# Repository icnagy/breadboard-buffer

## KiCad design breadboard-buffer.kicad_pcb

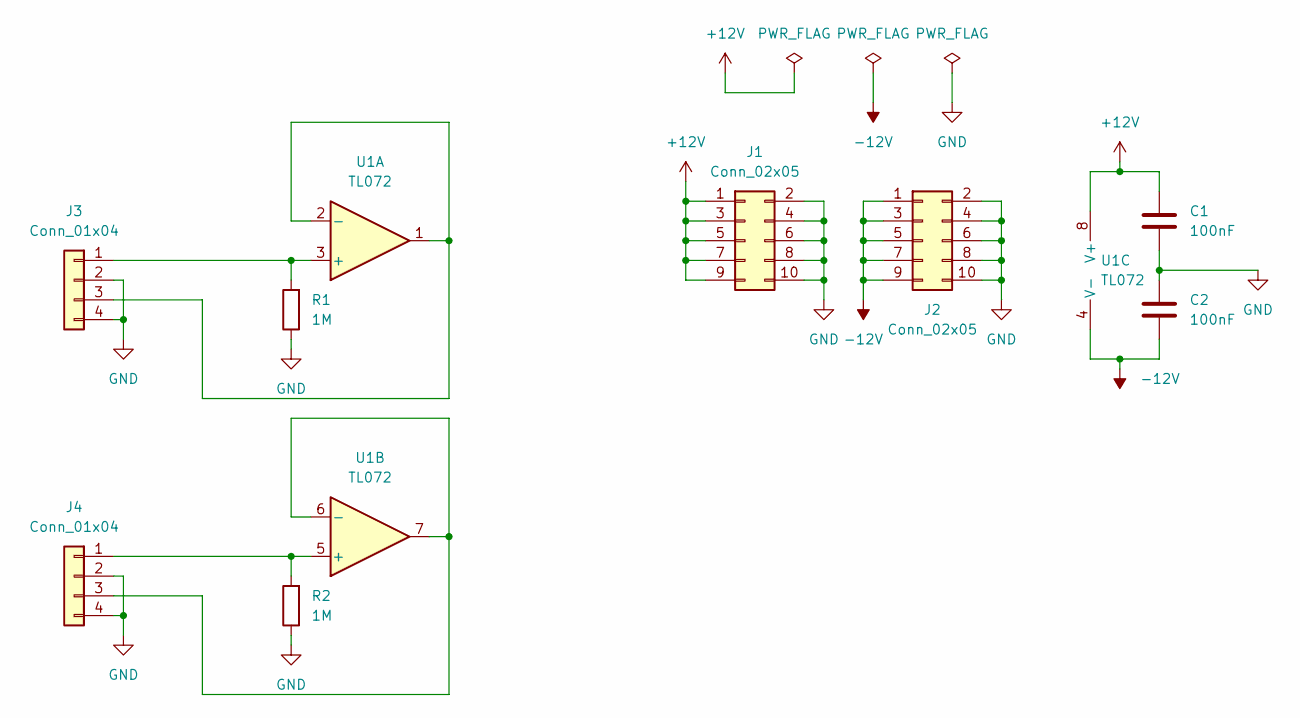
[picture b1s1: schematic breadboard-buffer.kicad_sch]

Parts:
C1, C2: 100nF; C_Disc_D4.7mm_W2.5mm_P5.00mm
J1, J2: Conn_02x05; PinHeader_2x05_P2.54mm_Vertical
J3, J4: Conn_01x04; PinHeader_1x04_P2.54mm_Vertical
R1, R2: 1M; R_Axial_DIN0207_L6.3mm_D2.5mm_P2.54mm_Vertical
U1: TL072; DIP-8_W7.62mm_Socket

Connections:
+12V: C1.1, J1.1, J1.3, J1.5, J1.7, J1.9, U1.8 (V+)
-12V: C2.2, J2.1, J2.3, J2.5, J2.7, J2.9, U1.4 (V-)
GND: C1.2, C2.1, J1.2, J1.4, J1.6, J1.8, J1.10, J2.2, J2.4, J2.6, J2.8, J2.10, J3.2, J3.4, J4.2, J4.4, R1.1, R2.1
unnamed: J3.1, R1.2, U1.3 (+)
unnamed: J3.3, U1.1, U1.2 (-)
unnamed: J4.1, R2.2, U1.5 (+)
unnamed: J4.3, U1.6 (-), U1.7

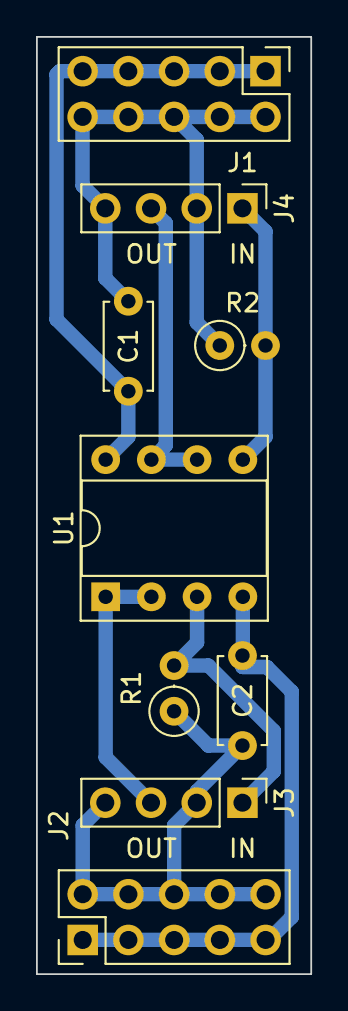
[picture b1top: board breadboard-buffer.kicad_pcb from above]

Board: 2 copper layers, 15.2 x 52.1 mm, 9 parts (0 on the bottom side), 7 nets.

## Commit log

2022-06-10 Add readme
2023-05-29 Kicad 7.0.5 upgrade
